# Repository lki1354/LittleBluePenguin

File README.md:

# LittleBluePenguin
The project is a one axis position control program written in Python 3.5. Additionally a visualizer of the sensor data is implemented.

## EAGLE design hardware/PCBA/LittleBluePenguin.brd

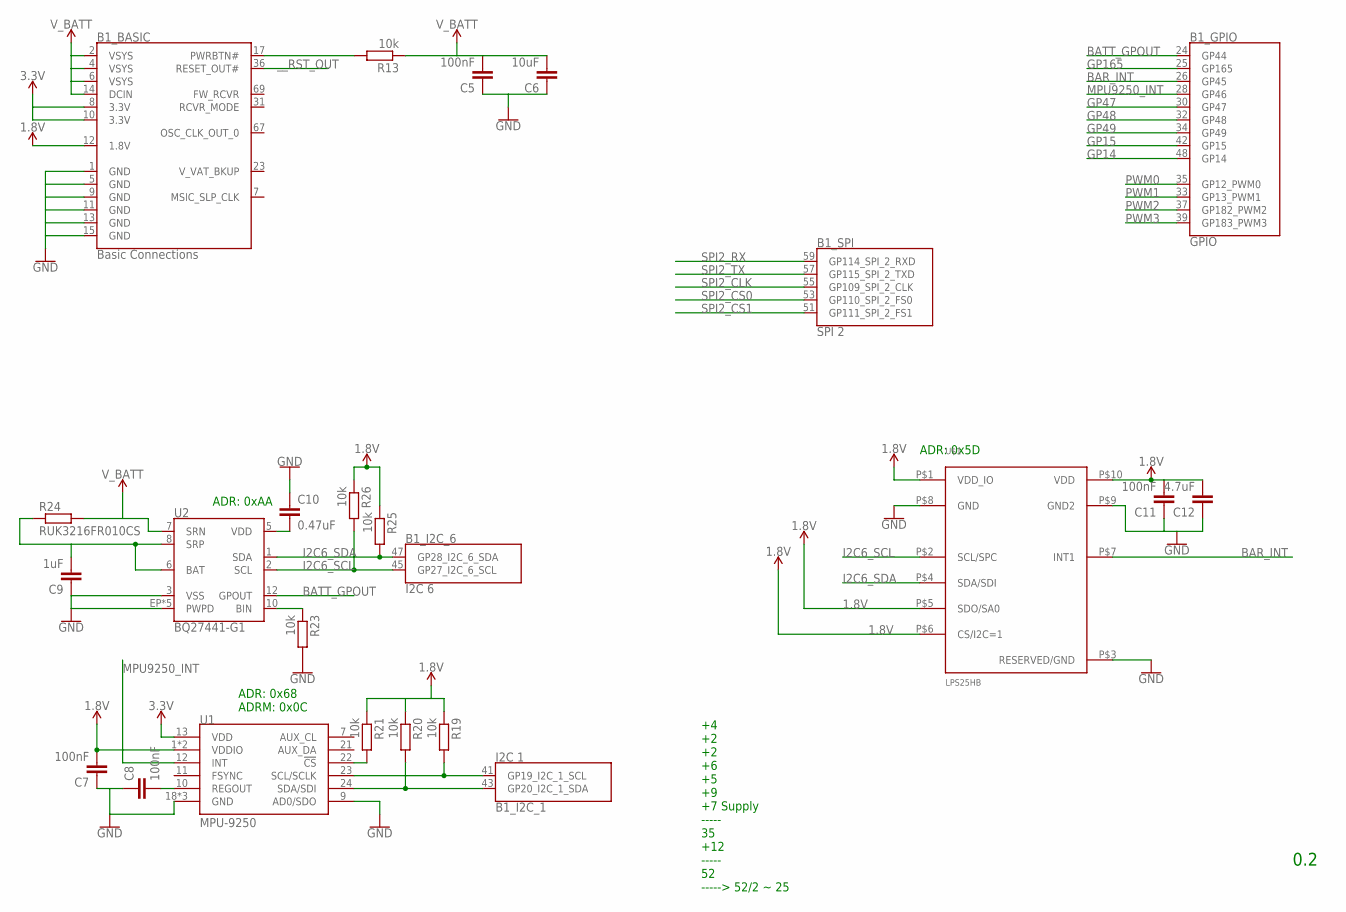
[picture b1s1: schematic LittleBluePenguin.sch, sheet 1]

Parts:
B1: SPARKFUN_EDISON; SPARKFUN_EDISON_DAUGHTER
C5, C7, C8, C11: 100nF; C0603K
C6: 10uF; C0603K
C9: 1uF; C0603K
C10: 0.47uF; C0603K
C12: 4.7uF; C0603K
R13, R19, R20, R21, R23, R25, R26: 10k; R0603
R24: RUK3216FR010CS; R1206
U1: MPU-9250; QFN24_PAD
U2: BQ27441-G1; PDSO-N12
U$1: LPS25HB; HLGA-10L

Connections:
1.8V: B1.12 (1.8V), C7.2, C11.2, C12.2, R19.1, R20.1, R21.1, R25.1, R26.1, U1.1 (VDDIO), U1.8 (VDDIO), U$1.P$1 (VDD_IO), U$1.P$5 (SDO/SA0), U$1.P$6 (CS/I2C=1), U$1.P$10 (VDD); also elsewhere on the board
3.3V: B1.8 (3.3V), B1.10 (3.3V), U1.13 (VDD); also elsewhere on the board
BAR_INT: B1.26 (GP45), U$1.P$7 (INT1)
BATT_GPOUT: B1.24 (GP44), U2.12 (GPOUT)
BATT_IN: C9.2, R24.1, U2.6 (BAT), U2.8 (SRP); also elsewhere on the board
GND: B1.1 (GND), B1.5 (GND), B1.9 (GND), B1.11 (GND), B1.13 (GND), B1.15 (GND), C5.1, C6.1, C7.1, C8.1, C9.1, C10.1, C11.1, C12.1, R23.2, U1.9 (AD0/SDO), U1.18 (GND), U1.20 (GND), U1.CENTER (GND), U2.3 (VSS), U2.EP (PWPD), U2.EP1 (PWPD), U2.EP2 (PWPD), U2.EP3 (PWPD), U2.EP4 (PWPD), U$1.P$3 (RESERVED/GND), U$1.P$8 (GND), U$1.P$9 (GND2); also elsewhere on the board
GP14: B1.48 (GP14)
GP15: B1.42 (GP15)
GP47: B1.30 (GP47)
GP48: B1.32 (GP48)
GP49: B1.34 (GP49)
GP165: B1.25 (GP165)
I2C1_SCL: B1.41 (GP19_I2C_1_SCL), R19.2, U1.23 (SCL/SCLK)
I2C1_SDA: B1.43 (GP20_I2C_1_SDA), R20.2, U1.24 (SDA/SDI)
I2C6_SCL: B1.45 (GP27_I2C_6_SCL), R26.2, U2.2 (SCL), U$1.P$2 (SCL/SPC); also elsewhere on the board
I2C6_SDA: B1.47 (GP28_I2C_6_SDA), R25.2, U2.1 (SDA), U$1.P$4 (SDA/SDI); also elsewhere on the board
MPU9250_INT: B1.28 (GP46), U1.12 (INT)
unnamed: R23.1, U2.10 (BIN)
unnamed: B1.17 (PWRBTN#), R13.2
unnamed: C8.2, U1.10 (REGOUT)
unnamed: R21.2, U1.22 (!CS)
unnamed: C10.2, U2.5 (VDD)
PWM0: B1.35 (GP12_PWM0); also elsewhere on the board
PWM1: B1.33 (GP13_PWM1); also elsewhere on the board
PWM2: B1.37 (GP182_PWM2); also elsewhere on the board
PWM3: B1.39 (GP183_PWM3); also elsewhere on the board
SPI2_CLK: B1.55 (GP109_SPI_2_CLK)
SPI2_CS0: B1.53 (GP110_SPI_2_FS0)
SPI2_CS1: B1.51 (GP111_SPI_2_FS1)
SPI2_RX: B1.59 (GP114_SPI_2_RXD)
SPI2_TX: B1.57 (GP115_SPI_2_TXD)
V_BATT: B1.2 (VSYS), B1.4 (VSYS), B1.6 (VSYS), B1.14 (DCIN), C5.2, C6.2, R13.1, R24.2, U2.7 (SRN); also elsewhere on the board
V_VAT_BKUP: B1.23 (V_VAT_BKUP)
__RST_OUT: B1.36 (RESET_OUT#); also elsewhere on the board

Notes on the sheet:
+4 +2 +2 +6 +5 +9 +7 Supply ----- 35 +12 ----- 52 -----> 52/2 ~ 25
ADR: 0x68 ADRM: 0x0C
ADR: 0xAA
ADR: 0x5D
0.2

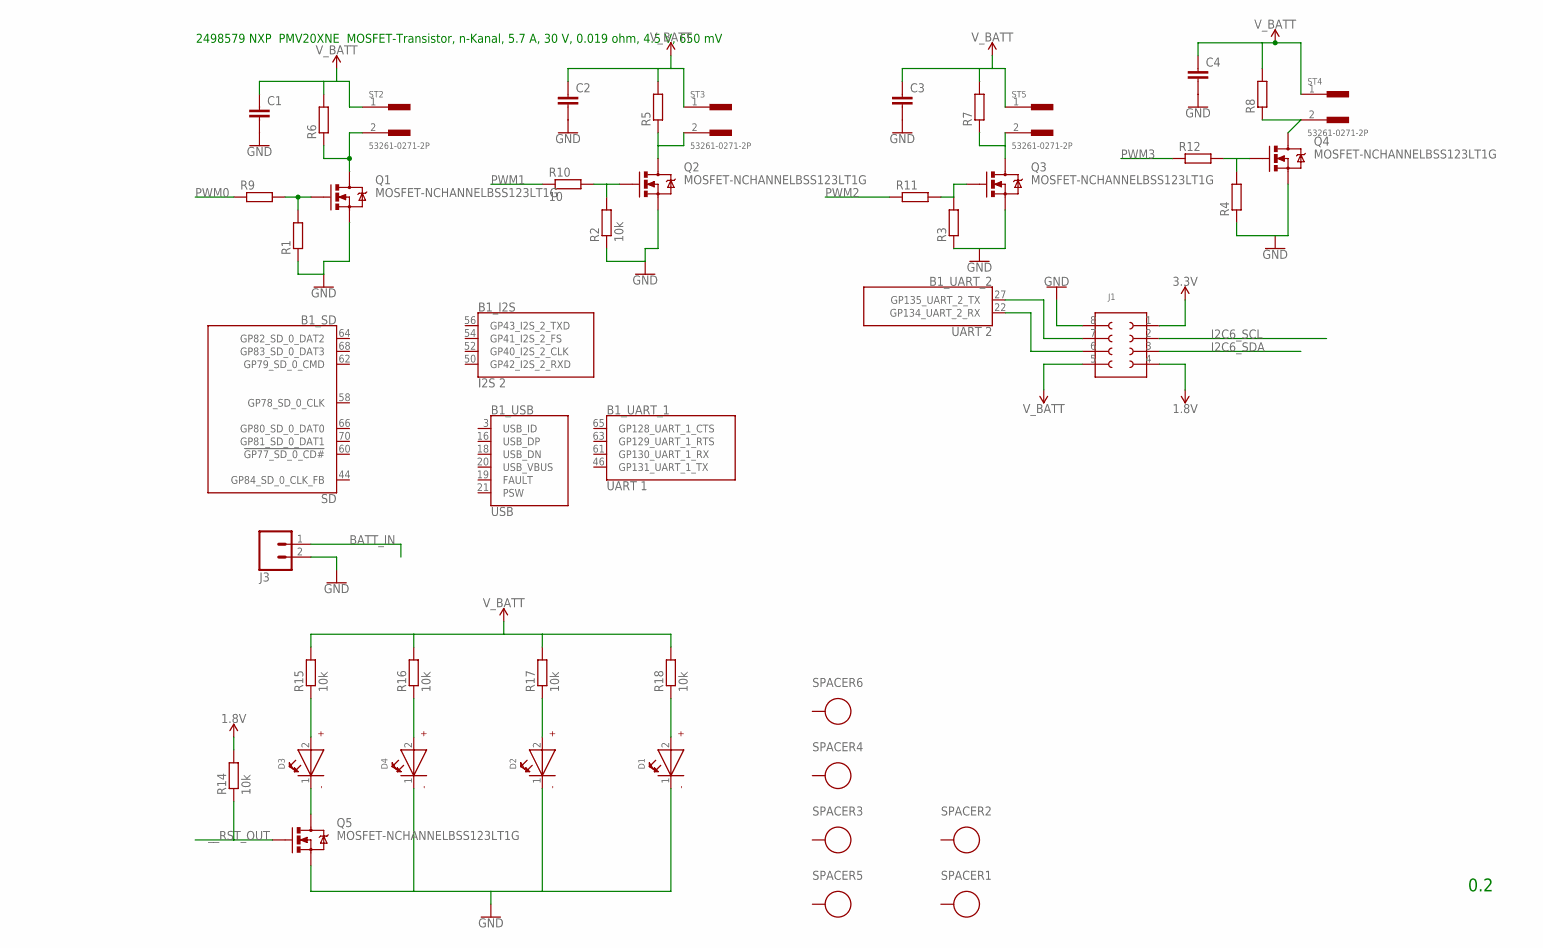
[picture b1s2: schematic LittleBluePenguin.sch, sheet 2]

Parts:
B1: SPARKFUN_EDISON; SPARKFUN_EDISON_DAUGHTER
C1, C2, C3, C4: C-EUC0603K; C0603K
D1, D2, D3, D4: WL-SMSW155124GS73200-G; 1204
J1: 623X0821021
J3: CONN_02JST-PTH-2; JST-2-PTH
Q1, Q2, Q3, Q4, Q5: MOSFET-NCHANNELBSS123LT1G; SOT23-3
R1, R3, R4, R5, R6, R7, R8, R9, R11, R12: R-EU_R0603; R0603
R2, R14, R15, R16, R17, R18: 10k; R0603
R10: 10; R0603
SPACER1, SPACER2: WA-SMSI_9774243; WA-SMSI_9774***243
SPACER3, SPACER4, SPACER5, SPACER6: WA-SMSI_9774360; WA-SMSI_9774***360
ST2, ST3, ST4, ST5: 53261-0271-2P; 53261-0271

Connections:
1.8V: J1.4 (5), R14.2; also elsewhere on the board
3.3V: J1.1 (8); also elsewhere on the board
BATT_IN: J3.1; also elsewhere on the board
GND: C1.2, C2.2, C3.2, C4.2, D1.1 (-), D2.1 (-), D4.1 (-), J1.8 (1), J3.2, Q1.2 (S), Q2.2 (S), Q3.2 (S), Q4.2 (S), Q5.2 (S), R1.1, R2.1, R3.1, R4.1; also elsewhere on the board
I2C6_SCL: J1.2 (7); also elsewhere on the board
I2C6_SDA: J1.3 (6); also elsewhere on the board
unnamed: Q3.1 (G), R3.2, R11.2
unnamed: Q1.3 (D), R6.1, ST2.2
unnamed: D3.1 (-), Q5.3 (D)
unnamed: D3.2 (+), R15.1
unnamed: Q1.1 (G), R1.2, R9.2
unnamed: Q2.1 (G), R2.2, R10.2
unnamed: Q3.3 (D), R7.1, ST5.2
unnamed: Q2.3 (D), R5.1, ST3.2
unnamed: D4.2 (+), R16.1
unnamed: D2.2 (+), R17.1
unnamed: Q4.1 (G), R4.2, R12.2
unnamed: Q4.3 (D), R8.1, ST4.2
unnamed: D1.2 (+), R18.1
unnamed: B1.27 (GP135_UART_2_TX), J1.7 (2)
unnamed: B1.22 (GP134_UART_2_RX), J1.6 (3)
PWM0: R9.1; also elsewhere on the board
PWM1: R10.1; also elsewhere on the board
PWM2: R11.1; also elsewhere on the board
PWM3: R12.1; also elsewhere on the board
V_BATT: C1.1, C2.1, C3.1, C4.1, J1.5 (4), R5.2, R6.2, R7.2, R8.2, R15.2, R16.2, R17.2, R18.2, ST2.1, ST3.1, ST4.1, ST5.1; also elsewhere on the board
V_VAT_BKUP: B1.23 (V_VAT_BKUP)
__RST_OUT: Q5.1 (G), R14.1; also elsewhere on the board

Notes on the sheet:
2498579 NXP PMV20XNE MOSFET-Transistor, n-Kanal, 5.7 A, 30 V, 0.019 ohm, 4.5 V, 650 mV
0.2

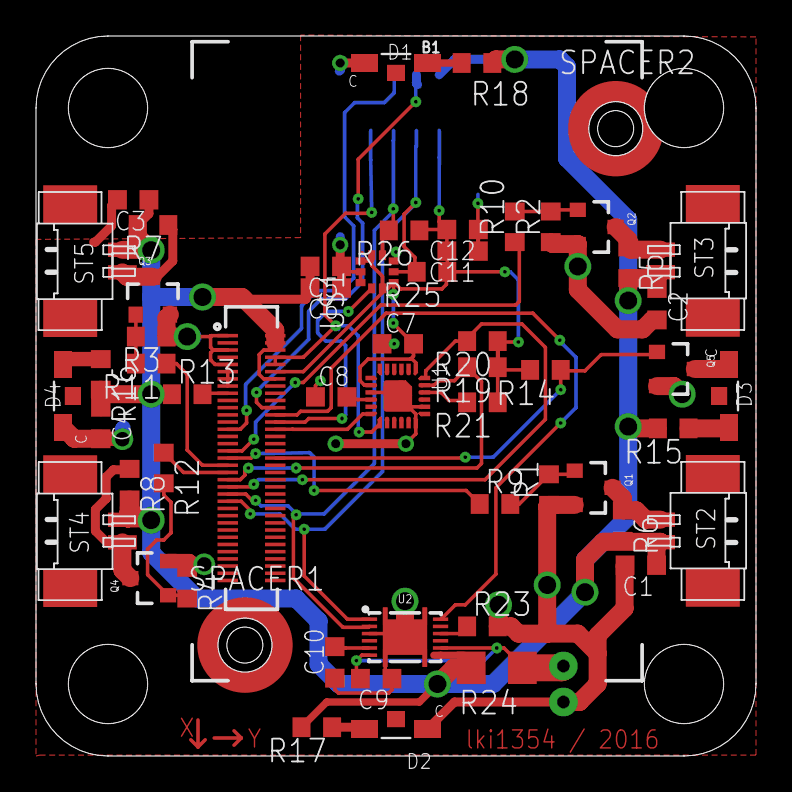
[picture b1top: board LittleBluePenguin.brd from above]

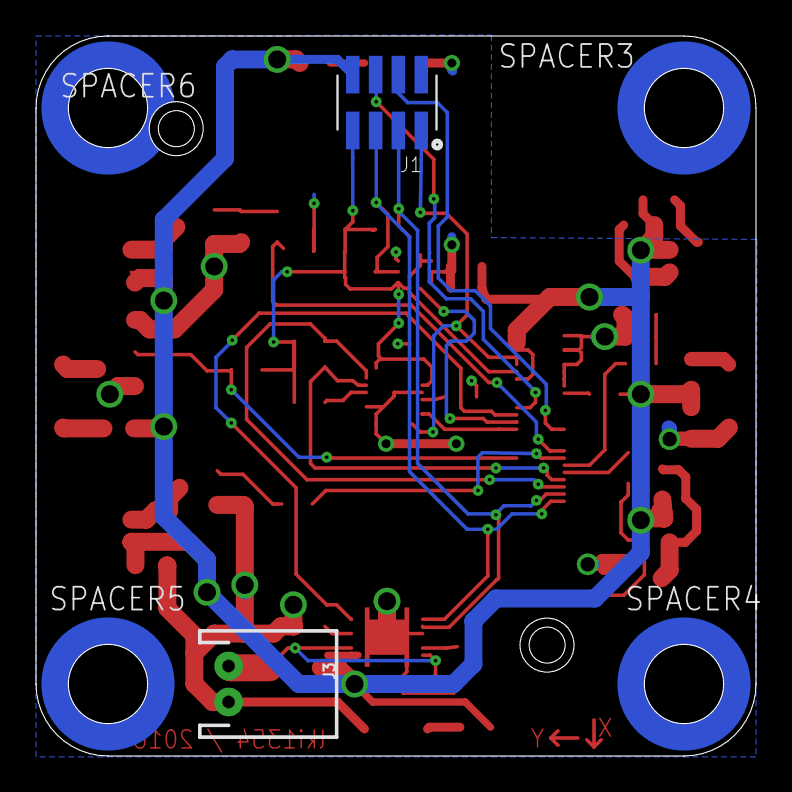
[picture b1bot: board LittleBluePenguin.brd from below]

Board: 2 copper layers, 40.0 x 40.0 mm, 62 parts (6 on the bottom side), 37 nets.

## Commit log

2017-03-19 add PCB files for the LBP
2017-03-19 change size of PCBA to show on main page
2017-03-19 add PCBA picture
2017-03-19 add missing ( and add title
2017-03-19 working pic. in readme
2017-03-21 add mpu9x50 module
2017-03-22 add test stand picture
2017-03-22 change picture in readme

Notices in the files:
parts and their libraries:
SparkFun-DiscreteSemi: Licensing: Creative Commons ShareAlike 4.0 International - https://creativecommons.org/licenses/by-sa/4.0
EAGLE-SPACER_STUDS_: Copyright: Würth Elektronik
